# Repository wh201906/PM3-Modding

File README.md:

# PM3 Modding

## PM3_Flash
Add the external SPI flash to the PM3 Easy  
[README](/PM3_Flash/README.md)  
[Schematic](./PM3_Flash/hardware/PM3_Flash-schematic.pdf)  

## PM3_ISO7816
Add the smartcard module to the PM3 Easy  
[README](/PM3_ISO7816/README.md)  
[Schematic](./PM3_ISO7816/hardware/PM3_ISO7816-schematic.pdf)  

## PM3_USB2TCP
[README](/PM3_USB2TCP/README.md)  
Connect to PM3 hardware with TCP, using ESP32-S3/S2 as a USB to TCP bridge  
No need to jumping any wires to the MCU directly. It works with most of the ESP32-S3/S2 dev boards  

## PM3_USB2UDP
[README](/PM3_USB2UDP/README.md)  
Connect to PM3 hardware with UDP, like `PM3_USB2TCP` but faster  

## License
All hardware projects in this repository are licensed under [CERN Open Hardware Licence Version 2 - Weakly Reciprocal](LICENSE.CERN-OHL-W).  
All software(firmware) projects in this repository are licensed under [GNU General Public License v3.0](LICENSE.GPL).

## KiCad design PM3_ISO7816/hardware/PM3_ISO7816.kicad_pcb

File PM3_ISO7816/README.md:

# PM3 ISO7816

Add the smartcard module to the Proxmark3 Easy.  

# Tips:
1. The MCU on the original smartcard module is Nuvoton's N76E003xQ20. I use the TSSOP-20 package(N76E003AT20) rather than QFN-20 package for easier manufacturing. The firmware works on both of them.
2. The firmware is separated into LDROM(kinda like bootloader) and APROM. To use this module, you need to flash the LDROM and APROM to the MCU first. 
3. The APROM can be found in the [Proxmark3 RRG repo](https://github.com/RfidResearchGroup/proxmark3/blob/v4.16717/client/resources/sim013.bin) with its [source code](https://github.com/RfidResearchGroup/proxmark3/blob/v4.16717/tools/simmodule/sim013.asm). The LDROM is [PM3_Modding/PM3_ISO7816/firmware/LDROM.bin](./firmware/LDROM.bin), which is closed-source and unreleased. I managed to get it from an original smartcard module.
4. You need to flash your Proxmark3 with smartcard module enabled firmware in order to use this module.

# Soldering

| Module | MCU  |
| ------ | ---- |
| VCC    | 3.3V |
| SDA    | PA7  |
| SCL    | PA5  |
| nRST   | PA1  |
| GND    | GND  |

Please refer to the datasheet of AT91SAM7Sxxx to find the physical position of these pins.  
For some of the old Proxmark3 Easy, the PA1 pin is exported near the JTAG pins. You only need to jump 2 wires(PA5, PA7) to the MCU directly.

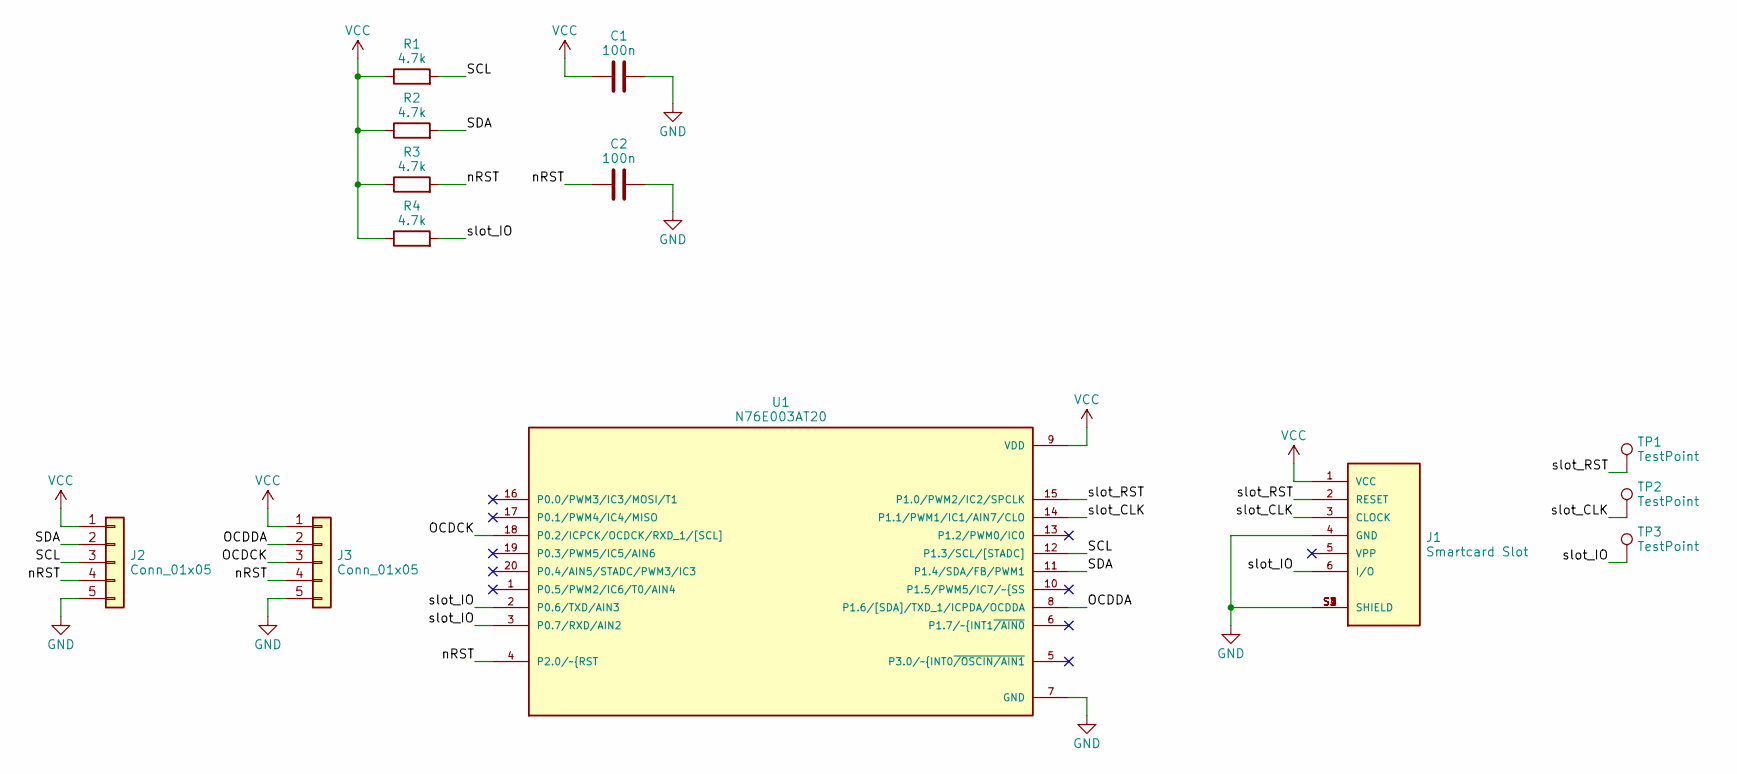
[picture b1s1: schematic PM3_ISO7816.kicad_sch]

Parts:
C1, C2: 100n; C_0603_1608Metric_Pad1.08x0.95mm_HandSolder
J1: Smartcard Slot; WURTH_693010020611; PARTREV F
J2, J3: Conn_01x05; PinHeader_1x05_P2.54mm_Vertical
R1, R2, R3, R4: 4.7k; R_0603_1608Metric_Pad0.98x0.95mm_HandSolder
TP1, TP2, TP3: TestPoint; TestPoint_Pad_D1.0mm
U1: N76E003AT20; SOP65P640X120-20N; PARTREV 1.04

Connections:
/OCDCK: J3.3, U1.18 (P0.2/ICPCK/OCDCK/RXD_1/[SCL])
/OCDDA: J3.2, U1.8 (P1.6/[SDA]/TXD_1/ICPDA/OCDDA)
/SCL: J2.3, R1.2, U1.12 (P1.3/SCL/[STADC])
/SDA: J2.2, R2.2, U1.11 (P1.4/SDA/FB/PWM1)
/nRST: C2.1, J2.4, J3.4, R3.2, U1.4 (P2.0/~RST~{)
/slot_CLK: J1.3 (CLOCK), TP2.1, U1.14 (P1.1/PWM1/IC1/AIN7/CLO)
/slot_IO: J1.6 (I/O), R4.2, TP3.1, U1.2 (P0.6/TXD/AIN3), U1.3 (P0.7/RXD/AIN2)
/slot_RST: J1.2 (RESET), TP1.1, U1.15 (P1.0/PWM2/IC2/SPCLK)
GND: C1.2, C2.2, J1.4 (GND), J1.S1 (SHIELD), J1.S2 (SHIELD), J1.S3 (SHIELD), J1.S4 (SHIELD), J2.5, J3.5, U1.7 (GND)
VCC: C1.1, J1.1 (VCC), J2.1, J3.1, R1.1, R2.1, R3.1, R4.1, U1.9 (VDD)

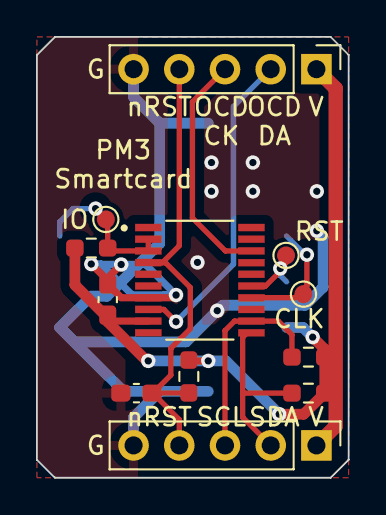
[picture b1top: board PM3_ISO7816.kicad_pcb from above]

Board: 2 copper layers, 17.3 x 24.5 mm, 13 parts (1 on the bottom side), 10 nets.

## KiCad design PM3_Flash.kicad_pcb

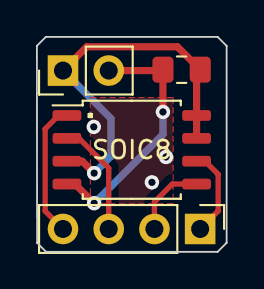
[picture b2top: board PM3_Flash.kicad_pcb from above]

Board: 2 copper layers, 10.5 x 11.9 mm, 4 parts (0 on the bottom side), 6 nets.

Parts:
C1: 100n; C_0805_2012Metric_Pad1.18x1.45mm_HandSolder
J1: Conn_01x02; PinHeader_1x02_P2.54mm_Vertical
J2: Conn_01x04; PinHeader_1x04_P2.54mm_Vertical
U1: W25Qxx; SOIC-8_5.23x5.23mm_P1.27mm

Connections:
/CLK: J2.1, U1.6 (CLK)
/CS: J2.4, U1.1 (~CS)
/MISO: J2.3, U1.2 (DO(IO1))
/MOSI: J2.2, U1.5 (DI(IO0))
GND: C1.2, J1.2, U1.4 (GND)
VCC: C1.1, J1.1, U1.3 (IO2), U1.7 (IO3), U1.8 (VCC)

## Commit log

2023-04-02 First version
2023-04-02 pcb: better layout
2023-04-03 10uF->100nF
2023-04-03 pcb: gerber output config for JLCPCB
2023-04-04 pcb: optimize filled zone
2023-06-16 Add project for Smartcard slot
2023-06-21 Smartcard: Add firmware and firmware dumper
2023-06-21 Smartcard: Misc work on PCB
    Swap VCC pin and GND pin to match the pin order of Nu-Link
    Change the footprint of sim card slot for hand soldering
    Add test points
2023-07-04 USB2TCP: Add base project
2023-07-04 USB2TCP: Open Proxmark3
    Set VID&PID for Proxmark3
    Use cdc_acm_host_open_vendor_specific()
    Remove unused code
2023-07-05 USB2TCP: Demo
    Based on:
    esp-idf-v5.0.2\examples\protocols\sockets\non_blocking
    esp-idf-v5.0.2\examples\peripherals\usb\host\cdc\cdc_acm_host
    esp-idf-v5.0.2\examples\wifi\getting_started\softAP
2023-07-06 Misc
    Move PM3_Flash hardware project to PM3_Flash/hardware/
    Add LICENSE
    Add README.md
2023-07-06 Add pictures
2023-08-29 Add schematic pdf
2023-08-29 Add README for each module
2023-08-29 Fix an error in README
    Bluetooth Classic is supported on ESP32-S3
    https://docs.espressif.com/projects/esp-idf/zh_CN/latest/esp32s3/api-reference/bluetooth/index.html
2023-09-09 Fix typo
2023-10-12 USB2TCP: Fixed the support for long packets
    Slightly faster now
2023-11-06 USB2UDP: Add project
    Faster than USB2TCP
2023-11-06 Change default port to 18888
2024-01-16 Fix README
2024-01-19 USB2UDP: Add Wifi station mode
    Faster than AP mode
2024-01-19 USB2UDP: Speed up
    Use usb_host_cdc_acm 2.x with configurable in_buffer_size
    Increase buffer size
    Replace ESP_LOGI() with printf() in RX/TX functions for less overhead
    Now the communication speed is higher than 200kByte/s, but this app
    still cannot support the real-time sampling due to the response time of
    packets.
2024-01-19 USB2UDP: Add static IP support in station mode
2024-01-20 USB2UDP: Fix some bugs
    Remove duplicate calls to esp_netif_init()
    Fix a deleted line
    Keep UDP socket alive if the errno is EAGAIN
2024-01-20 USB2TCP: Apply changes from USB2UDP
    From:
    commit 802f700ba82fae288bfdcc3b76f7ac163e3ee7fd
    commit da60cc311849981c28d874ea1f5d1336404f0a1f
    commit cb4072ead64cac6db27412ef75d6a978f8586e7b
    commit b806c8f10350a6b2b6db0749399d6da61b53b231
    `lf sniff` and `hw status` doesn't work in the Wifi station mode.
2024-01-20 Add CI for the bridge firmware
2024-01-21 Use Kconfig
